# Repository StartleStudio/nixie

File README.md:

# nixie
Repo for the nixie project

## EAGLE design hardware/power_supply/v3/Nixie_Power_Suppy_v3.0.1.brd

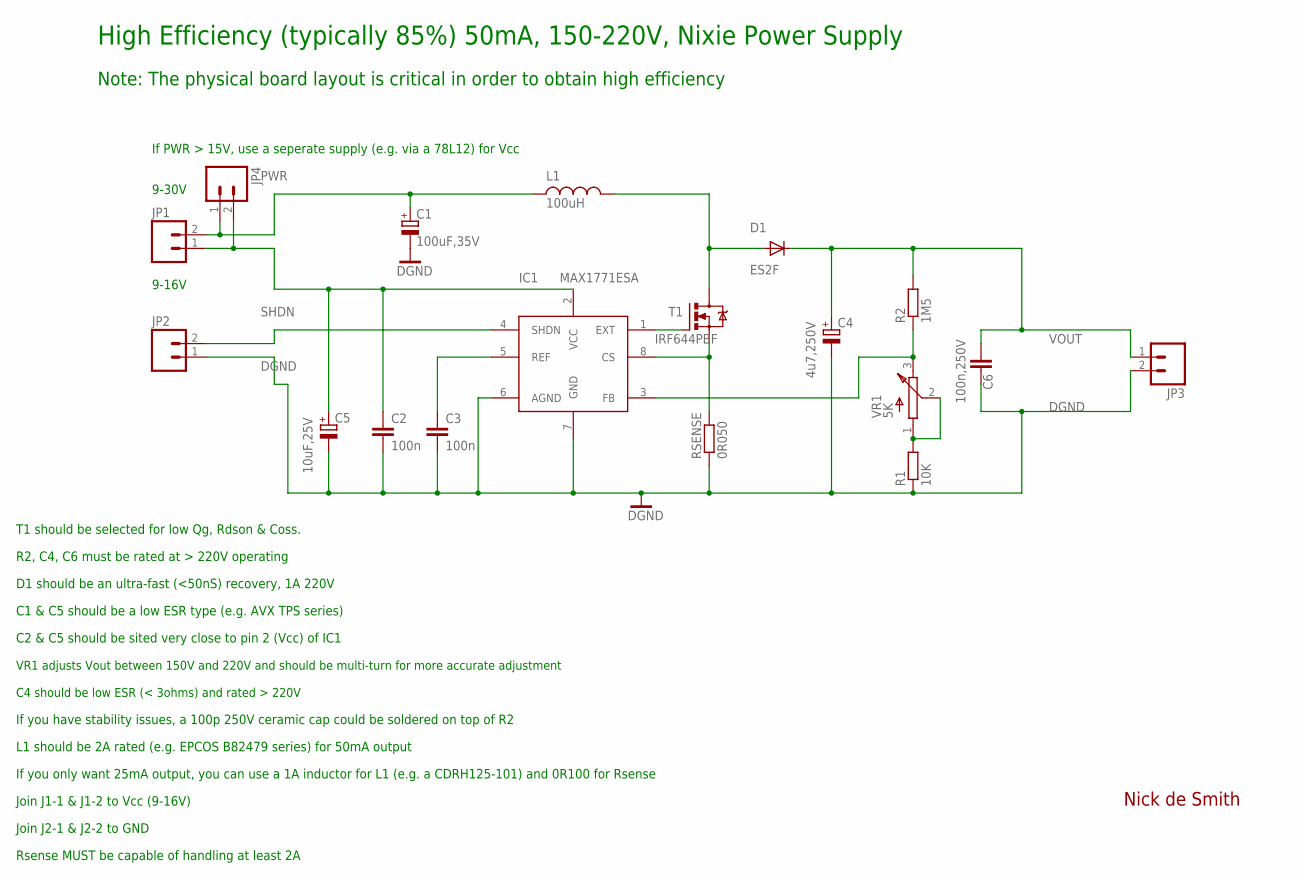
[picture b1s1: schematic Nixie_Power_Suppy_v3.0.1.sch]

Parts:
C1: 100uF,35V; C-EIA-7343
C2, C3: 100n; C0805
C4: 4u7,250V; NICHICON-UJ-12
C5: 10uF,25V; C-EIA-7343
C6: 100n,250V; C2420
D1: ES2F; SMC
IC1: MAX1771ESA; SO-8
JP1, JP2, JP3, JP4: M02PTH; 1X02
L1: 100uH; L-B82479
R1: 10K; R0805
R2: 1M5; R2512
RSENSE: 0R050; R2010
T1: IRF644PBF; TO220BV
VR1: 5K; BOURNS-3214W

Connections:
DGND: C1.-, C2.2, C3.2, C4.1 (-), C5.-, C6.P$2 (2), IC1.6 (AGND), IC1.7 (GND), JP2.1, JP3.2, R1.1, RSENSE.1
EXT: IC1.1 (EXT), T1.G
unnamed: IC1.8 (CS), RSENSE.2, T1.S
unnamed: R1.2, VR1.1 (A), VR1.2 (W)
unnamed: IC1.3 (FB), R2.1, VR1.3 (B)
unnamed: D1.A, L1.P$2 (2), T1.D
unnamed: C3.1, IC1.5 (REF)
PWR: C1.+, JP1.2, JP4.1, L1.P$1 (1)
SHDN: IC1.4 (SHDN), JP2.2
VCC: C2.1, C5.+, IC1.2 (VCC), JP1.1, JP4.2
VOUT: C4.2 (+), C6.P$1 (1), D1.C, JP3.1, R2.2

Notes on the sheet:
R2, C4, C6 must be rated at > 220V operating
D1 should be an ultra-fast (<50nS) recovery, 1A 220V
C1 & C5 should be a low ESR type (e.g. AVX TPS series)
C2 & C5 should be sited very close to pin 2 (Vcc) of IC1
Nick de Smith
VR1 adjusts Vout between 150V and 220V and should be multi-turn for more accurate adjustment
C4 should be low ESR (< 3ohms) and rated > 220V
If you have stability issues, a 100p 250V ceramic cap could be soldered on top of R2
L1 should be 2A rated (e.g. EPCOS B82479 series) for 50mA output
Join J1-1 & J1-2 to Vcc (9-16V)
Join J2-1 & J2-2 to GND
T1 should be selected for low Qg, Rdson & Coss.
Rsense MUST be capable of handling at least 2A
High Efficiency (typically 85%) 50mA, 150-220V, Nixie Power Supply
9-16V
9-30V
If PWR > 15V, use a seperate supply (e.g. via a 78L12) for Vcc
Note: The physical board layout is critical in order to obtain high efficiency
If you only want 25mA output, you can use a 1A inductor for L1 (e.g. a CDRH125-101) and 0R100 for Rsense

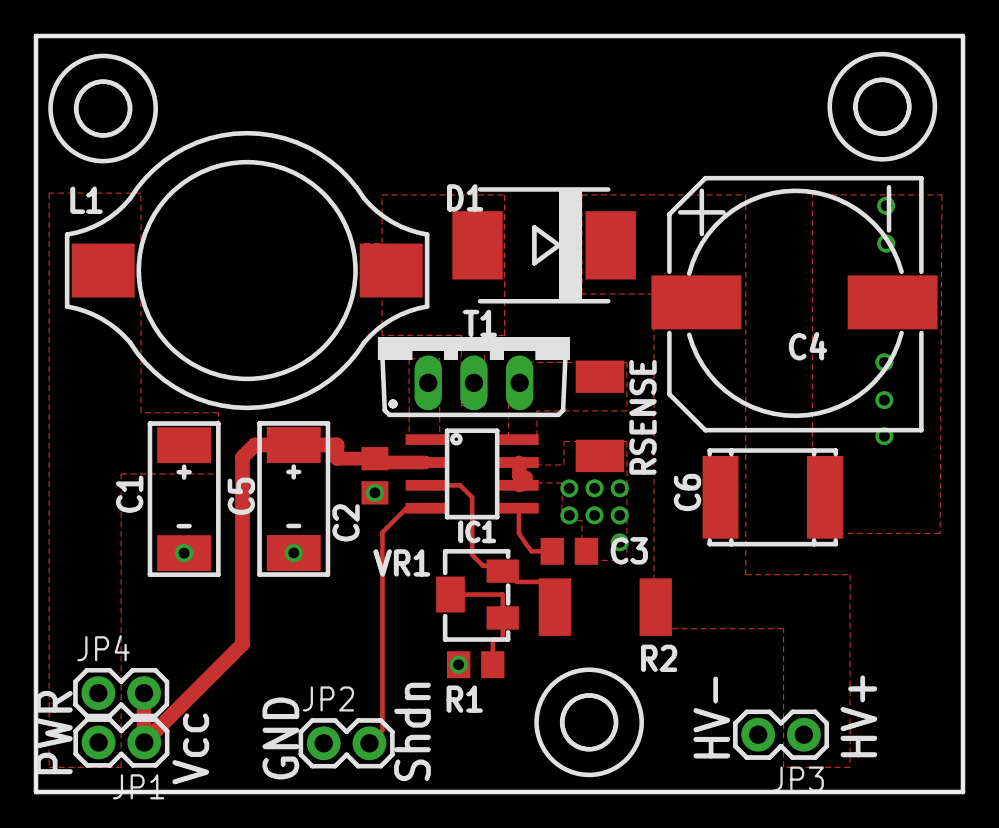
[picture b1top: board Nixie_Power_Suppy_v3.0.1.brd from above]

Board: 2 copper layers, 51.5 x 42.0 mm, 21 parts (0 on the bottom side), 11 nets.

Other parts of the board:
U$2, U$3, U$4: 2,8

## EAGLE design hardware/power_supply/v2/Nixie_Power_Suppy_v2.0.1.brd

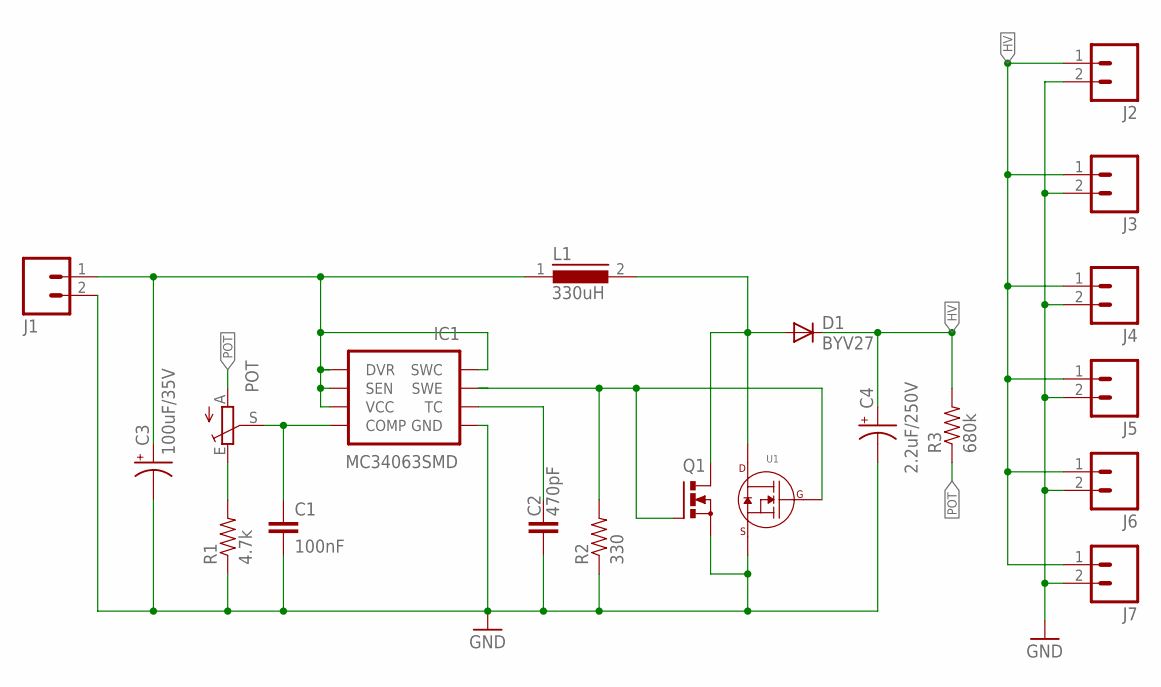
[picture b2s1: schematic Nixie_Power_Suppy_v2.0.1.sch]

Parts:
C1: 100nF; 0805
C2: 470pF; 0805
C3: 100uF/35V; CPOL-RADIAL-100UF-25V
C4: 2.2uF/250V; CPOL-RADIAL-100UF-25V
D1: BYV27; SOD57-10
IC1: MC34063SMD; SO08
J1, J2, J3, J4, J5, J6, J7: M02LOCK; 1X02_LOCK
L1: 330uH; DR74
POT: TRIM_EU-CA6V; CA6V
Q1: PMOSFET_NTO220BV; TO220BV
R1: 4.7k; 0805
R2: 330; 0805
R3: 680k; 0805
U1: MOSFET_N-CHANNEL_SINGLE_TO-252-3; TO-252-3

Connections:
GND: C1.2, C2.2, C3.2 (-), C4.2 (-), IC1.4 (GND), J1.2, J2.2, J3.2, J4.2, J5.2, J6.2, J7.2, Q1.S, R1.1, R2.1, U1.3 (SOURCE)
HV: C4.1 (+), D1.C, J2.1, J3.1, J4.1, J5.1, J6.1, J7.1, R3.2
unnamed: POT.E, R1.2
unnamed: C1.1, IC1.5 (COMP), POT.S
unnamed: C3.1 (+), IC1.1 (SWC), IC1.6 (VCC), IC1.7 (SEN), IC1.8 (DVR), J1.1, L1.1
unnamed: D1.A, L1.2, Q1.D, U1.PAD (DRAIN)
unnamed: C2.1, IC1.3 (TC)
unnamed: IC1.2 (SWE), Q1.G, R2.2, U1.1 (GATE)
POT: POT.A, R3.1

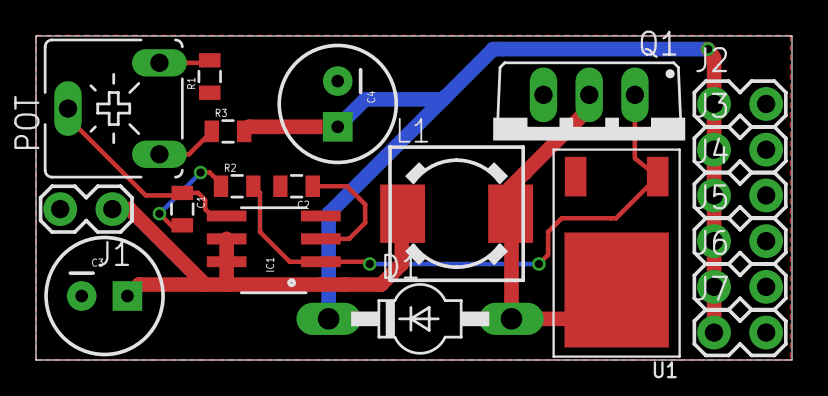
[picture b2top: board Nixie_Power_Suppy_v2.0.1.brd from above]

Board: 2 copper layers, 42.0 x 18.0 mm, 20 parts (0 on the bottom side), 9 nets.

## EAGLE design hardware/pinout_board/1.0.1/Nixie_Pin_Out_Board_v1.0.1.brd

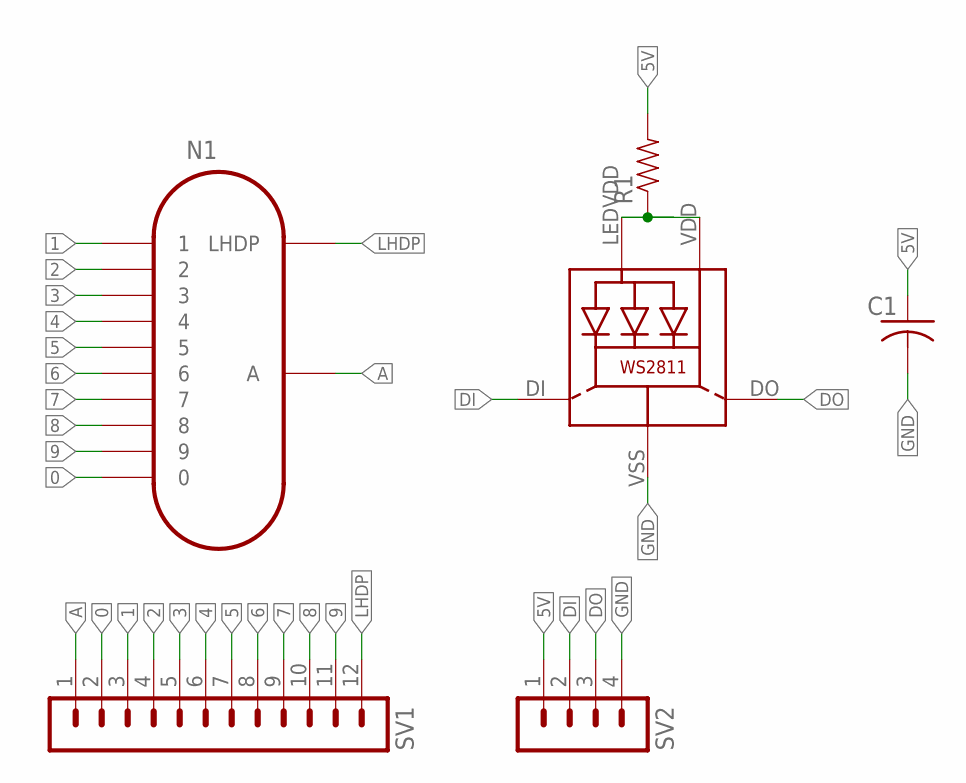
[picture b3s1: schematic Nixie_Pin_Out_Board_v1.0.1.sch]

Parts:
C1: C-USC0805K; C0805K
LED1: WS28115050
N1: IN-12B; IN-12
R1: RESISTOR0805-RES; 0805
SV1: MA12-1
SV2: MA04-1

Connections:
0: N1.0, SV1.2
1: N1.1, SV1.3
2: N1.2, SV1.4
3: N1.3, SV1.5
4: N1.4, SV1.6
5: N1.5, SV1.7
5V: C1.1, R1.2, SV2.1
6: N1.6, SV1.8
7: N1.7, SV1.9
8: N1.8, SV1.10
9: N1.9, SV1.11
A: N1.A, SV1.1
DI: LED1.DI, SV2.2
DO: LED1.DO, SV2.3
GND: C1.2, LED1.VSS (GND), SV2.4
LHDP: N1.LHDP, SV1.12
WIRE1: LED1.LEDVDD, LED1.VDD, R1.1

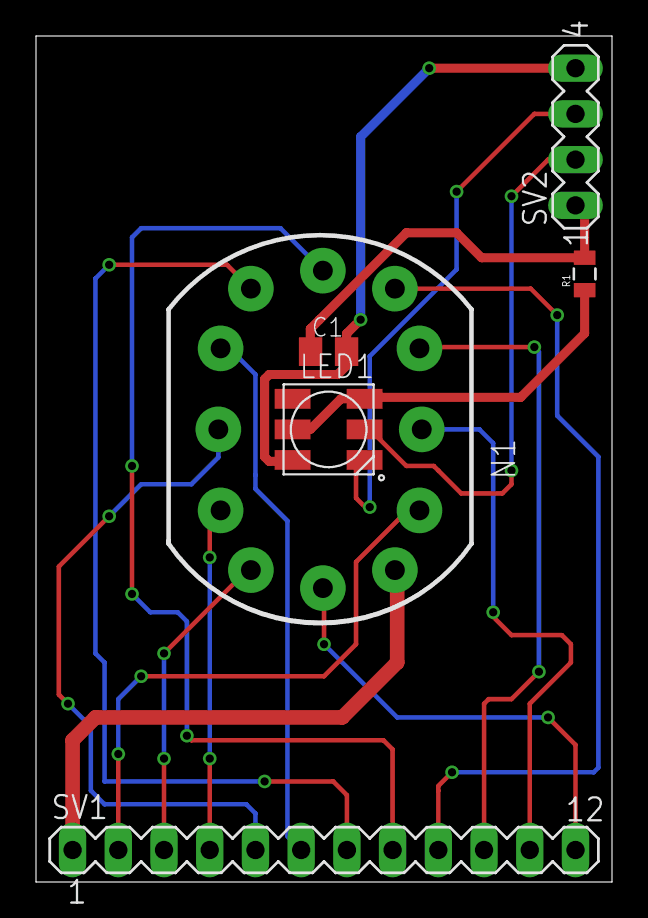
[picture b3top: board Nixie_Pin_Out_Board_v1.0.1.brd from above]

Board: 2 copper layers, 32.0 x 47.0 mm, 6 parts (0 on the bottom side), 17 nets.

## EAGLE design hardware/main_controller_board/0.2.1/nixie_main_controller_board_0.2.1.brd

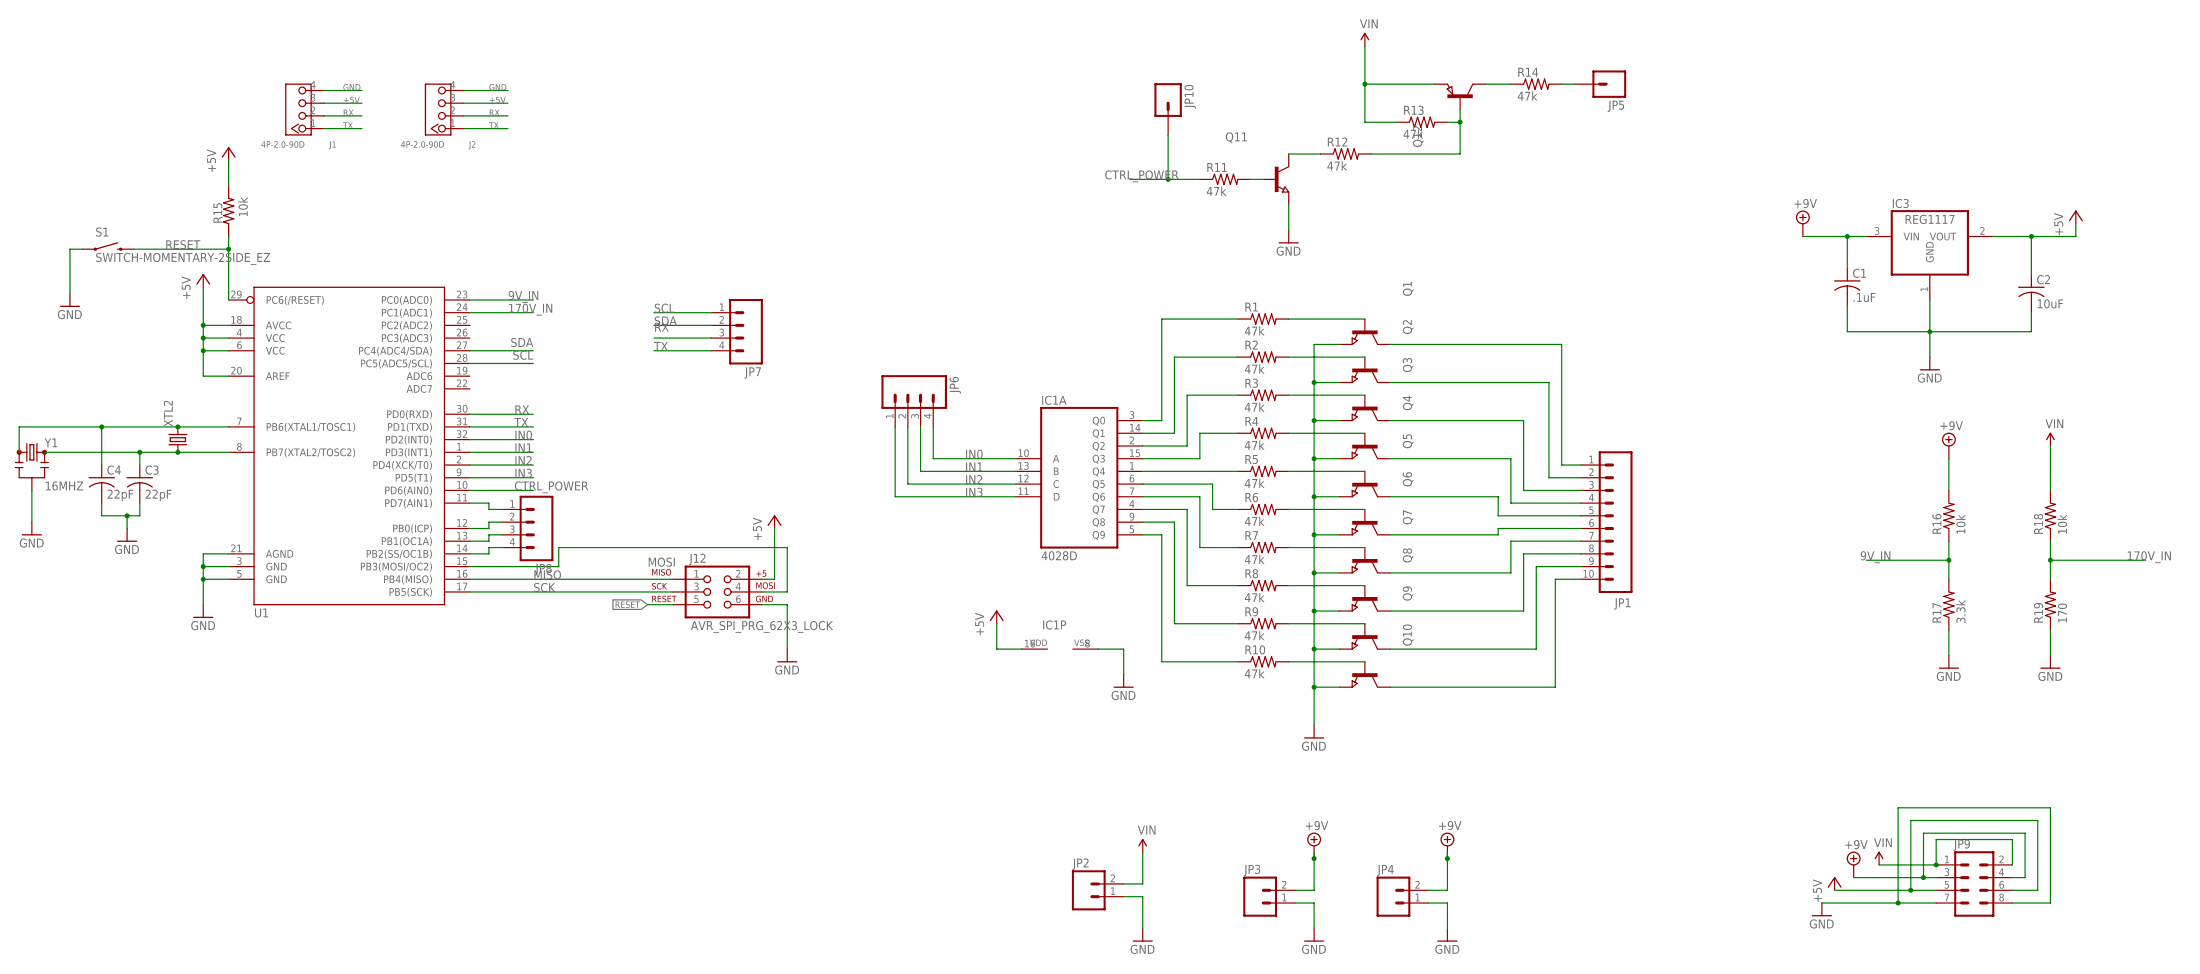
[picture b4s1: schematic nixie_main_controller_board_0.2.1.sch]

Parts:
C1: .1uF; C0603
C2: 10uF; C0805
C3, C4: 22pF; C0603
IC1: 4028D; SO16
IC3: REG1117; SOT223
J1, J2: 4P-2.0-90D; HW4-2.0-90D
J12: AVR_SPI_PRG_62X3_LOCK; 2X3_LOCK
JP1: M10LOCK; 1X10_LOCK
JP2, JP3, JP4: M02LOCK; 1X02_LOCK
JP5, JP10: M01PTH; 1X01
JP6, JP7, JP8: M04PTH; 1X04
JP9: M04X2; 2X4
Q1, Q2, Q3, Q4, Q5, Q6, Q7, Q8, Q9, Q10, Q11: NPN-TRANSISTOR_SOT23; SOT23
Q12: PNP-TRANSISTOR_SOT23; SOT23
R1, R2, R3, R4, R5, R6, R7, R8, R9, R10, R11, R12, R13, R14: 47k; R0603
R15: 10k; 0603
R16, R18: 10k; R0603
R17: 3.3k; R0603
R19: 170; R0603
S1: SWITCH-MOMENTARY-2SIDE_EZ; TACTILE-PTH-SIDEEZ
U1: ATMEGA328_SMT; TQFP32-08
XTL2: CRYSTALHC49S; HC49/S
Y1: 16MHZ; RESONATOR-SMD

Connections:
9V_IN: R16.1, R17.2, U1.23 (PC0(ADC0))
170V_IN: R18.1, R19.2, U1.24 (PC1(ADC1))
+5V: C2.1, IC1.16 (VDD), IC3.2 (VOUT), J1.3, J2.3, J12.2, JP9.5, JP9.6, R15.2, U1.4 (VCC), U1.6 (VCC), U1.18 (AVCC), U1.20 (AREF)
+9V: C1.1, IC3.3 (VIN), JP3.2, JP4.2, JP9.3, JP9.4, R16.2
CTRL_POWER: JP10.1, R11.1, U1.10 (PD6(AIN0))
GND: C1.2, C2.2, C3.2, C4.2, IC1.8 (VSS), IC3.1 (GND), J1.4, J2.4, J12.6, JP2.1, JP3.1, JP4.1, JP9.7, JP9.8, Q1.2 (E), Q2.2 (E), Q3.2 (E), Q4.2 (E), Q5.2 (E), Q6.2 (E), Q7.2 (E), Q8.2 (E), Q9.2 (E), Q10.2 (E), Q11.2 (E), R17.1, R19.1, S1.1, U1.3 (GND), U1.5 (GND), U1.21 (AGND), Y1.2
IN0: IC1.10 (A), JP6.4, U1.32 (PD2(INT0))
IN1: IC1.13 (B), JP6.3, U1.1 (PD3(INT1))
IN2: IC1.12 (C), JP6.2, U1.2 (PD4(XCK/T0))
IN3: IC1.11 (D), JP6.1, U1.9 (PD5(T1))
MISO: J12.1, U1.16 (PB4(MISO))
MOSI: J12.4, U1.15 (PB3(MOSI/OC2))
unnamed: IC1.3 (Q0), R1.1
unnamed: Q1.1 (B), R1.2
unnamed: IC1.14 (Q1), R2.1
unnamed: IC1.2 (Q2), R3.1
unnamed: Q2.1 (B), R2.2
unnamed: Q3.1 (B), R3.2
unnamed: Q4.1 (B), R4.2
unnamed: Q5.1 (B), R5.2
unnamed: Q6.1 (B), R6.2
unnamed: Q7.1 (B), R7.2
unnamed: Q8.1 (B), R8.2
unnamed: Q9.1 (B), R9.2
unnamed: Q10.1 (B), R10.2
unnamed: IC1.15 (Q3), R4.1
unnamed: IC1.1 (Q4), R5.1
unnamed: IC1.5 (Q9), R10.1
unnamed: IC1.9 (Q8), R9.1
unnamed: IC1.4 (Q7), R8.1
unnamed: IC1.7 (Q6), R7.1
unnamed: IC1.6 (Q5), R6.1
unnamed: JP1.1, Q1.3 (C)
unnamed: JP1.2, Q2.3 (C)
unnamed: JP1.3, Q3.3 (C)
unnamed: JP1.4, Q4.3 (C)
unnamed: JP1.5, Q5.3 (C)
unnamed: JP1.6, Q6.3 (C)
unnamed: JP1.7, Q7.3 (C)
unnamed: JP1.8, Q8.3 (C)
unnamed: JP1.9, Q9.3 (C)
unnamed: JP1.10, Q10.3 (C)
unnamed: C4.1, U1.7 (PB6(XTAL1/TOSC1)), XTL2.2, Y1.1
unnamed: C3.1, U1.8 (PB7(XTAL2/TOSC2)), XTL2.1, Y1.3
unnamed: Q11.1 (B), R11.2
unnamed: Q11.3 (C), R12.1
unnamed: JP8.1, U1.11 (PD7(AIN1))
unnamed: JP8.2, U1.12 (PB0(ICP))
unnamed: Q12.1 (B), R12.2, R13.2
unnamed: Q12.3 (C), R14.1
unnamed: JP5.1, R14.2
unnamed: JP8.3, U1.13 (PB1(OC1A))
unnamed: JP8.4, U1.14 (PB2(SS/OC1B))
RESET: J12.5, R15.1, S1.2, U1.29 (PC6(/RESET))
RX: J1.2, J2.2, JP7.3, U1.30 (PD0(RXD))
SCK: J12.3, U1.17 (PB5(SCK))
SCL: JP7.1, U1.28 (PC5(ADC5/SCL))
SDA: JP7.2, U1.27 (PC4(ADC4/SDA))
TX: J1.1, J2.1, JP7.4, U1.31 (PD1(TXD))
VIN: JP2.2, JP9.1, JP9.2, Q12.2 (E), R13.1, R18.2

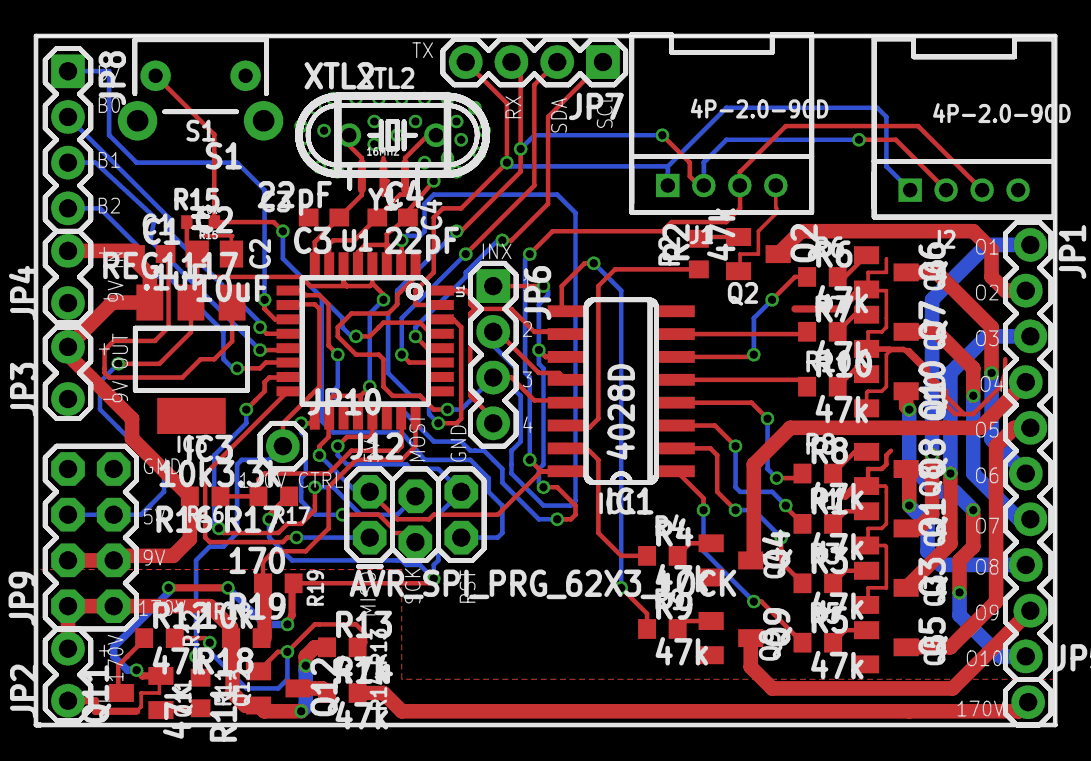
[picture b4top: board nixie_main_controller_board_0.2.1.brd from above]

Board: 2 copper layers, 56.6 x 38.3 mm, 54 parts (0 on the bottom side), 60 nets.

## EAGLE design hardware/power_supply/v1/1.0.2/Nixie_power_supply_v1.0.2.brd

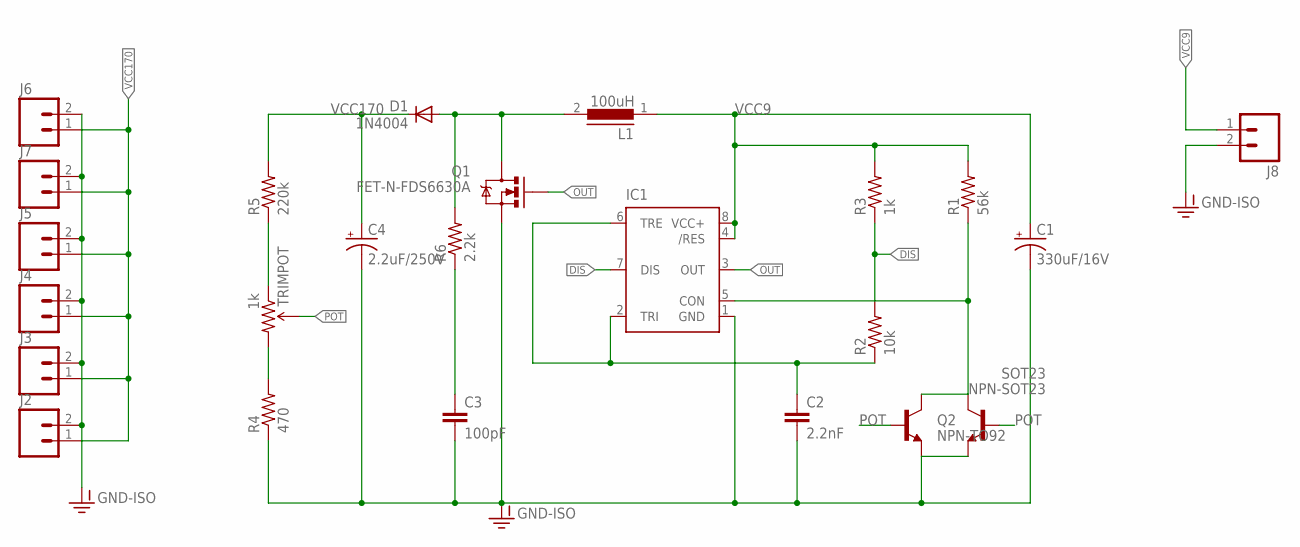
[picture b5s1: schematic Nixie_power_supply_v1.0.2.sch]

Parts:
C1: 330uF/16V; E3,5-8
C2: 2.2nF; 0805
C3: 100pF; C1005
C4: 2.2uF/250V; CPOL-RADIAL-100UF-25V
D1: 1N4004; DO41-10
IC1: NE555D; SO08
J2, J3, J4, J5, J6, J7, J8: M02LOCK; 1X02_LOCK
L1: 100uH; DR74
Q1: FET-N-FDS6630A; SO08
Q2: NPN-TO92; TO-92-AMMO
R1: 56k; 0805
R2: 10k; 0805
R3: 1k; 0805
R4: 470; 0805
R5: 220k; R1206
R6: 2.2k; R1206
SOT23: NPN-SOT23; SOT23-BEC
TRIMPOT: 1k; TRIMPOT_TC33

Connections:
C2: C2.1, IC1.2 (TRI), IC1.6 (TRE), R2.1
DIS: IC1.7 (DIS), R2.2, R3.1
GND-ISO: C1.-, C2.2, C3.2, C4.2 (-), IC1.1 (GND), J2.2, J3.2, J4.2, J5.2, J6.2, J7.2, J8.2, Q1.1 (S), Q1.2 (S), Q1.3 (S), Q2.3 (E), R4.1, SOT23.E
unnamed: D1.A, L1.2, Q1.5 (D), Q1.6 (D), Q1.7 (D), Q1.8 (D), R6.2
unnamed: C3.1, R6.1
unnamed: R5.1, TRIMPOT.1 (CCW)
unnamed: R4.2, TRIMPOT.3 (CW)
unnamed: IC1.5 (CON), Q2.1 (C), R1.1, SOT23.C
OUT: IC1.3 (OUT), Q1.4 (G)
POT: Q2.2 (B), SOT23.B, TRIMPOT.2 (WIPER)
VCC9: C1.+, IC1.4 (/RES), IC1.8 (VCC+), J8.1, L1.1, R1.2, R3.2
VCC170: C4.1 (+), D1.C, J2.1, J3.1, J4.1, J5.1, J6.1, J7.1, R5.2

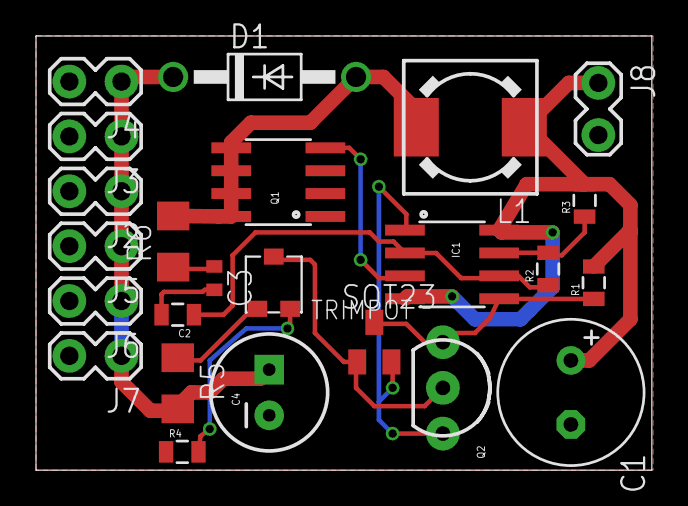
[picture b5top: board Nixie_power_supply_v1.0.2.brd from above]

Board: 2 copper layers, 34.2 x 24.1 mm, 24 parts (0 on the bottom side), 12 nets.

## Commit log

2016-06-07 controller firmware 1.0
2016-06-09 added code for on/off
2016-06-09 added hex file

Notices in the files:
parts and their libraries:
SparkFun-Connectors: Licensing: Creative Commons ShareAlike 4.0 International - https://creativecommons.org/licenses/by-sa/4.0
SparkFun-DigitalIC: Licensing: CC v3.0 Share-Alike You are welcome to use this library for commercial purposes.
